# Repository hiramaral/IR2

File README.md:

# IR2
Documentos de minha Tese de Doutorado

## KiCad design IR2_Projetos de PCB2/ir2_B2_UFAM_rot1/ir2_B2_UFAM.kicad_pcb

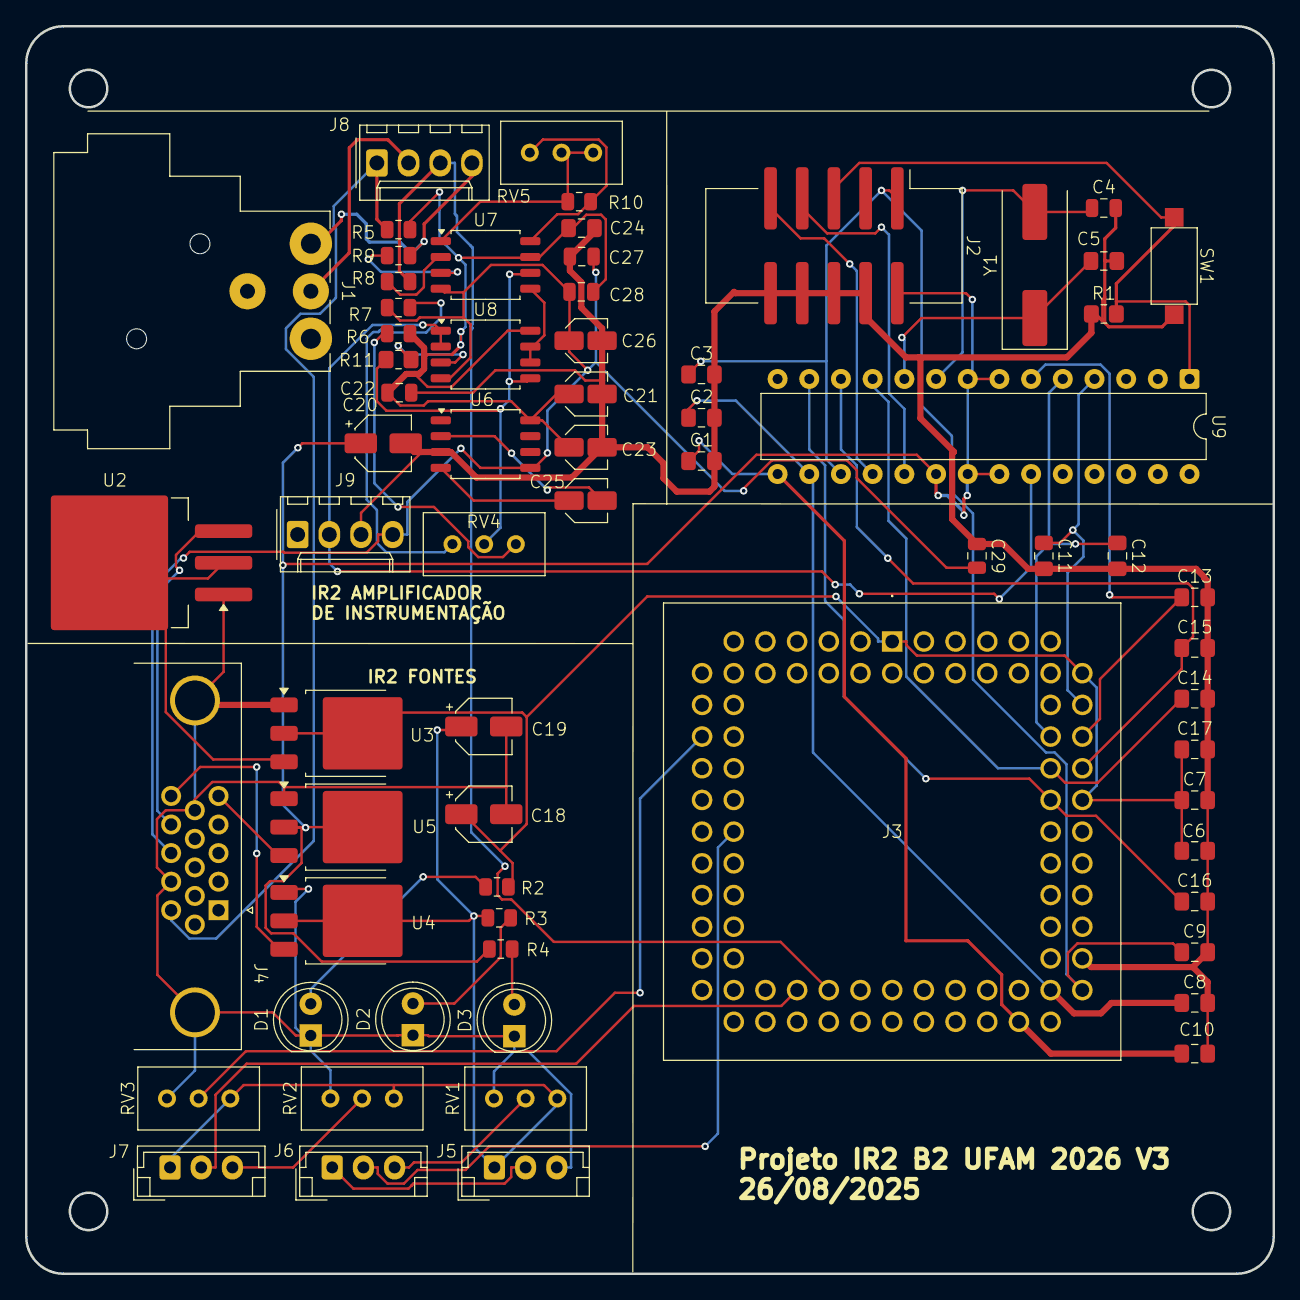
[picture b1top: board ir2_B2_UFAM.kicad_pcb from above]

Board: 4 copper layers, 100.0 x 100.0 mm, 67 parts (0 on the bottom side), 48 nets.

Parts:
C1, C2, C3, C6, C7, C8, C9, C10, C11, C12, C13, C14, C15, C16, C17, C24: 100nF; C_0805_2012Metric_Pad1.18x1.45mm_HandSolder
C4: 22pF; C_0805_2012Metric
C5: 22pF; C_0805_2012Metric_Pad1.18x1.45mm_HandSolder
C18, C19, C20: 22uF; CP_Elec_4x5.8
C21, C23, C25, C26: 10uF; C_Elec_3x5.4
C22, C27, C28, C29: 100nF; C_0805_2012Metric
D1, D2, D3: LED; LED_D5.0mm
J1: NC3MBH-B; Jack_XLR_Neutrik_NC3MBH-B_Horizontal
J2: USBAsp; IDC-Header_2x05_P2.54mm_Vertical_SMD
J3: IR2_UFAM_V0_PLCC84; ir2_J3_UFAM_PLCC84AT
J4: DE15_Socket_HighDensity_MountingHoles; DSUB-15-HD_Socket_Horizontal_P2.29x1.90mm_EdgePinOffset3.03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
J5, J6, J7: Conn_01x03_Pin; JST_EH_B3B-EH-A_1x03_P2.50mm_Vertical
J8: Entrada; Molex_KK-254_AE-6410-04A_1x04_P2.54mm_Vertical
J9: Saída; Molex_KK-254_AE-6410-04A_1x04_P2.54mm_Vertical
R1: 10K; R_0805_2012Metric_Pad1.20x1.40mm_HandSolder
R2, R3, R4: 220R; R_0805_2012Metric
R5: 10R; R_0805_2012Metric
R6, R7, R8, R9: 1K; R_0805_2012Metric
R10: 49,4kR; R_0805_2012Metric
R11: 1K; R_0805_2012Metric_Pad1.20x1.40mm_HandSolder
RV1, RV2, RV3, RV4: 10K; Potentiometer_Bourns_3296W_Vertical
RV5: 100K; Potentiometer_Bourns_3296W_Vertical
SW1: IR2_UFAM; SW_SPST_CK_RS282G05A3
U2: AZ1084-5.0; TO-263-3_TabPin2
U3, U4, U5: AZ1084-3.3; TO-252-3_TabPin2
U6: LMC7660; SOIC-8_5.3x5.3mm_P1.27mm
U7: AD620; SOIC-8_5.3x5.3mm_P1.27mm
U8: ir2_U8_LM358; ir2_U8_SOIC-8_5.3x5.3mm_P1.27mm
U9: ir2_U1_Atmega328P; DIP-28_W7.62mm
Y1: 16MHz; Crystal_SMD_HC49-SD

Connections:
3,3V: C20.1, J2.2, R4.1, U5.2 (VO), U9.7 (VCC), U9.8 (GND), U9.20 (AVCC), U9.21 (AREF), U9.22 (GND)
+8V4: J4.14, U2.3 (VI)
+12V: J4.11, J8.1, R5.1
-12V: C26.1, C27.1, C28.1, C29.2, J4.13, J9.4, R7.1, U6.5 (VOUT), U7.4 (Vs-), U8.4 (GND)
/A0: C11.1, J3.72 (A0), U9.4 (A0)
/A1: C12.1, J3.71 (A1), U9.5 (A1)
/A2: C13.1, J3.70 (A2), U9.6 (A2)
/AC0: C14.1, J3.69 (AC0), U9.11 (AC0)
/AC1: C15.1, J3.68 (AC1), U9.12 (AC1)
/AC2: C16.1, J3.67 (AC2), U9.13 (AC2)
/Fontes/3V3IR2: C6.1, C7.1, C17.1, C18.1, J3.1 (VDD_ANA), J3.66 (MOD_1), J3.74 (VDD_DIG), R2.2, U3.2 (VO)
/MISO: J2.9, U9.18 (MISO)
/MODO E_RST E_RDR/3V3: C19.1, J5.1, J7.1, R3.1, RV1.1, RV2.1, RV3.1, U4.2 (VO)
/MODO E_RST E_RDR/E_RDR: J3.38 (E_RDR), J7.2
/MODO E_RST E_RDR/E_RST: J3.23 (E_RST), J6.2
/MODO E_RST E_RDR/V_LOAD: J3.16 (V_LOAD), RV3.2
/Módulo Amplificador de Instrumentação/S+: J1.1, J8.4, R9.2
/Módulo Amplificador de Instrumentação/S-: J3.40 (OUT_G), J8.3, R8.2
/Módulo Amplificador de Instrumentação/VOUT: J9.2, U8.1 (1OUT), U8.2 (1IN-), U9.23 (OUT_G)
/RESET: J2.5, R1.2, SW1.1, U9.1 (~RESET/PC6)
/RWS: C3.1, C9.1, J2.1, J3.54 (RWS), U9.17 (RWS)
/SCK: J2.7, U9.19 (SCK)
GND: C1.2, C2.2, C3.2, C4.2, C5.2, C6.2, C7.2, C8.2, C9.2, C10.2, C11.2, C12.2, C13.2, C14.2, C15.2, C16.2, C17.2, C18.2, C19.2, C20.2, C21.2, C22.2, C23.2, C24.2, C26.2, C27.2, C29.1, D1.1 (K), D2.1 (K), D3.1 (K), J1.2, J1.3, J1.G, J2.4, J2.6, J2.8, J2.10, J3.39 (GND), J3.56 (GND_DIG), J4.0, J4.10, J4.12, J5.3, J8.2, J9.1, J9.3, R1.1, RV1.3, RV2.3, RV3.3, SW1.2, U2.1 (GND), U3.1 (GND), U4.1 (GND), U5.1 (GND), U6.3 (GND)
unnamed: J4.5, U5.3 (VI)
unnamed: J4.15, U4.3 (VI)
unnamed: D1.2 (A), R2.1
unnamed: D2.2 (A), R3.2
unnamed: D3.2 (A), R4.2
unnamed: C2.1, C8.1, J3.55 (RDR), U9.16 (RDR)
unnamed: C1.1, C10.1, J3.51 (RST), U9.15 (RST)
unnamed: J5.2, J6.1
unnamed: J6.3, RV1.2
unnamed: J7.3, RV2.2
unnamed: R6.1, RV4.1
unnamed: R7.2, RV4.3
unnamed: R10.1, RV5.1, RV5.2, U7.1 (Rg)
unnamed: R10.2, RV5.3, U7.8 (Rg)
unnamed: U2.2 (VO), U3.3 (VI)
unnamed: C25.2, U6.2 (CAP+)
unnamed: C25.1, U6.4 (CAP-)
unnamed: C21.1, C22.1, C23.1, C24.1, C28.2, R5.2, R6.2, U6.8 (V+), U7.7 (Vs+), U8.8 (VCC)
unnamed: R9.1, U7.3 (+)
unnamed: R8.1, U7.2 (-)
unnamed: U7.5 (Ref), U8.6 (2IN-), U8.7 (2OUT)
unnamed: R11.2, U8.3 (1IN+)
unnamed: R11.1, RV4.2, U7.6, U8.5 (2IN+)
unnamed: C4.1, U9.9 (XTAL1/PB6), Y1.2
unnamed: C5.1, U9.10 (XTAL2/PB7), Y1.1

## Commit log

2025-08-24 first commit
    Inicial commit to IR2 Project
2025-08-24 commit 2
    Digitação e atualização teste
2025-08-24 Alterado 3D da placa.
2025-08-30 Ir2 update Hiram
    Update IR2 2025
